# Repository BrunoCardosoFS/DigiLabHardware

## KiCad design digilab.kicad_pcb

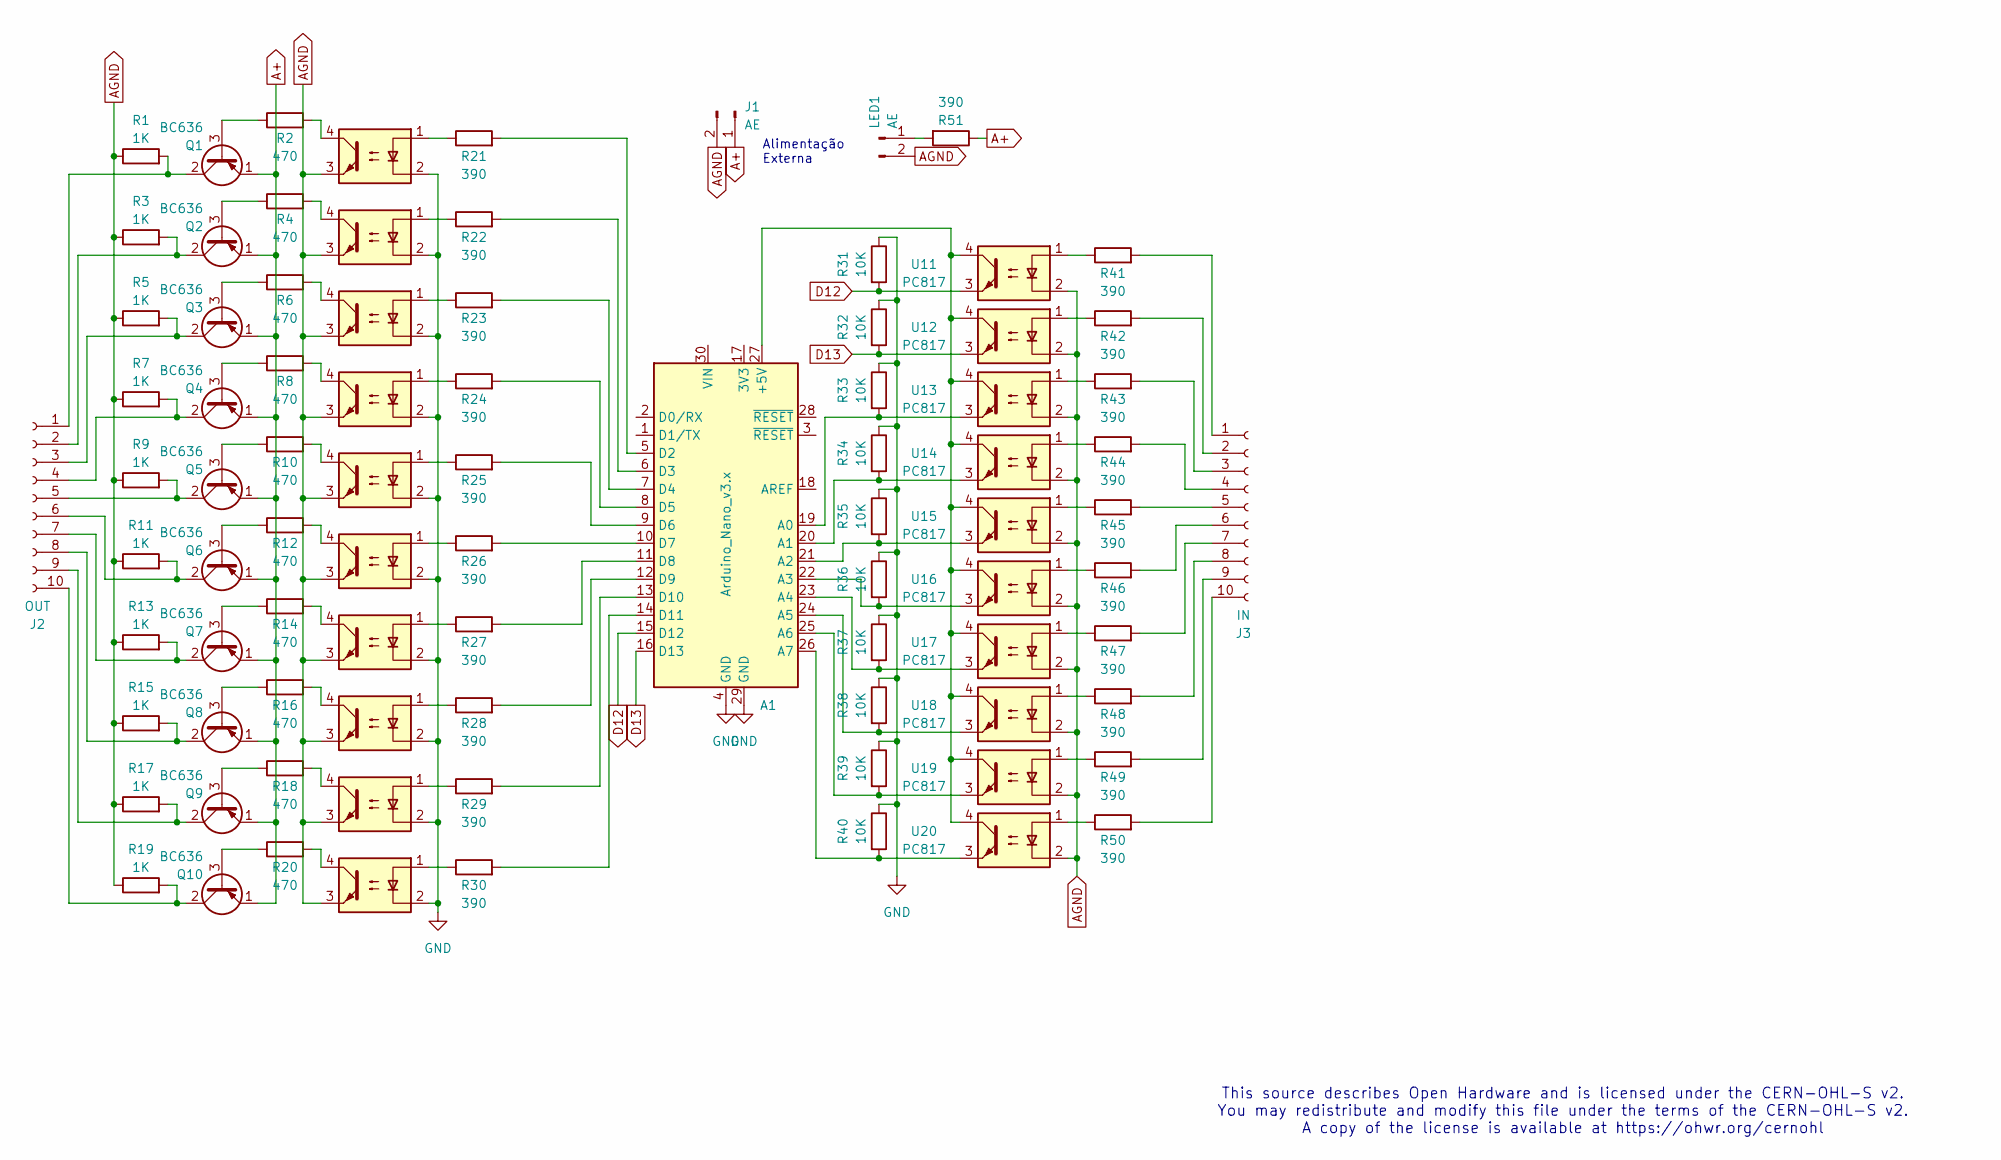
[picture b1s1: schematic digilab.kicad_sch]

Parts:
A1: Arduino_Nano_v3.x; Arduino_Nano
J1: AE; PinHeader_1x02_P2.54mm_Vertical
J2: OUT; PinSocket_1x10_P2.54mm_Vertical
J3: IN; PinSocket_1x10_P2.54mm_Vertical
LED1: AE; PinHeader_1x02_P2.54mm_Vertical
Q1, Q2, Q3, Q4, Q5, Q6, Q7, Q8, Q9, Q10: BC636; TO-92_Wide
R1, R3, R5, R7, R9, R11, R13, R15, R17, R19: 1K; R_Axial_DIN0204_L3.6mm_D1.6mm_P7.62mm_Horizontal
R2, R4, R6, R8, R10, R12, R14, R16, R18, R20: 470; R_Axial_DIN0204_L3.6mm_D1.6mm_P7.62mm_Horizontal
R21, R22, R23, R24, R25, R26, R27, R28, R29, R30, R41, R42, R43, R44, R45, R46, R47, R48, R49, R50, R51: 390; R_Axial_DIN0204_L3.6mm_D1.6mm_P7.62mm_Horizontal
R31, R32, R33, R34, R35, R36, R37, R38, R39, R40: 10K; R_Axial_DIN0204_L3.6mm_D1.6mm_P7.62mm_Horizontal
U1, U2, U3, U4, U5, U6, U7, U8, U9, U10, U11, U12, U13, U14, U15, U16, U17, U18, U19, U20: PC817; DIP-4_W7.62mm

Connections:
A+: J1.1, Q1.1 (E), Q2.1 (E), Q3.1 (E), Q4.1 (E), Q5.1 (E), Q6.1 (E), Q7.1 (E), Q8.1 (E), Q9.1 (E), Q10.1 (E), R51.1
AGND: J1.2, LED1.2, R1.1, R3.1, R5.1, R7.1, R9.1, R11.1, R13.1, R15.1, R17.1, R19.1, U1.3, U2.3, U3.3, U4.3, U5.3, U6.3, U7.3, U8.3, U9.3, U10.3, U11.2, U12.2, U13.2, U14.2, U15.2, U16.2, U17.2, U18.2, U19.2, U20.2
D12: A1.15 (D12), R31.2, U11.3
D13: A1.16 (D13), R32.2, U12.3
GND: A1.4 (GND), A1.29 (GND), R31.1, R32.1, R33.1, R34.1, R35.1, R36.1, R37.1, R38.1, R39.1, R40.1, U1.2, U2.2, U3.2, U4.2, U5.2, U6.2, U7.2, U8.2, U9.2, U10.2
unnamed: A1.27 (+5V), U11.4, U12.4, U13.4, U14.4, U15.4, U16.4, U17.4, U18.4, U19.4, U20.4
unnamed: A1.19 (A0), R33.2, U13.3
unnamed: A1.20 (A1), R34.2, U14.3
unnamed: A1.21 (A2), R35.2, U15.3
unnamed: A1.22 (A3), R36.2, U16.3
unnamed: A1.23 (A4), R37.2, U17.3
unnamed: A1.24 (A5), R38.2, U18.3
unnamed: A1.25 (A6), R39.2, U19.3
unnamed: A1.26 (A7), R40.2, U20.3
unnamed: A1.5 (D2), R21.2
unnamed: A1.6 (D3), R22.2
unnamed: A1.7 (D4), R23.2
unnamed: A1.8 (D5), R24.2
unnamed: A1.9 (D6), R25.2
unnamed: A1.10 (D7), R26.2
unnamed: A1.11 (D8), R27.2
unnamed: A1.12 (D9), R28.2
unnamed: A1.13 (D10), R29.2
unnamed: A1.14 (D11), R30.2
unnamed: J2.1, Q1.2 (C), R1.2
unnamed: J2.2, Q2.2 (C), R3.2
unnamed: J2.3, Q3.2 (C), R5.2
unnamed: J2.4, Q4.2 (C), R7.2
unnamed: J2.5, Q5.2 (C), R9.2
unnamed: J2.6, Q6.2 (C), R11.2
unnamed: J2.7, Q7.2 (C), R13.2
unnamed: J2.8, Q8.2 (C), R15.2
unnamed: J2.9, Q9.2 (C), R17.2
unnamed: J2.10, Q10.2 (C), R19.2
unnamed: J3.1, R41.2
unnamed: J3.2, R42.2
unnamed: J3.3, R43.2
unnamed: J3.4, R44.2
unnamed: J3.5, R45.2
unnamed: J3.6, R46.2
unnamed: J3.7, R47.2
unnamed: J3.8, R48.2
unnamed: J3.9, R49.2
unnamed: J3.10, R50.2
unnamed: LED1.1, R51.2
unnamed: Q1.3 (B), R2.1
unnamed: Q2.3 (B), R4.1
unnamed: Q3.3 (B), R6.1
unnamed: Q4.3 (B), R8.1
unnamed: Q5.3 (B), R10.1
unnamed: Q6.3 (B), R12.1
unnamed: Q7.3 (B), R14.1
unnamed: Q8.3 (B), R16.1
unnamed: Q9.3 (B), R18.1
unnamed: Q10.3 (B), R20.1
unnamed: R2.2, U1.4
unnamed: R4.2, U2.4
unnamed: R6.2, U3.4
unnamed: R8.2, U4.4
unnamed: R10.2, U5.4
unnamed: R12.2, U6.4
unnamed: R14.2, U7.4
unnamed: R16.2, U8.4
unnamed: R18.2, U9.4
unnamed: R20.2, U10.4
unnamed: R21.1, U1.1
unnamed: R22.1, U2.1
unnamed: R23.1, U3.1
unnamed: R24.1, U4.1
unnamed: R25.1, U5.1
unnamed: R26.1, U6.1
unnamed: R27.1, U7.1
unnamed: R28.1, U8.1
unnamed: R29.1, U9.1
unnamed: R30.1, U10.1
unnamed: R41.1, U11.1
unnamed: R42.1, U12.1
unnamed: R43.1, U13.1
unnamed: R44.1, U14.1
unnamed: R45.1, U15.1
unnamed: R46.1, U16.1
unnamed: R47.1, U17.1
unnamed: R48.1, U18.1
unnamed: R49.1, U19.1
unnamed: R50.1, U20.1

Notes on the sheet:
Alimentação Externa
This source describes Open Hardware and is licensed under the CERN-OHL-S v2. You may redistribute and modify this file under the terms of the CERN-OHL-S v2. A copy of the license is available at https://ohwr.org/cernohl

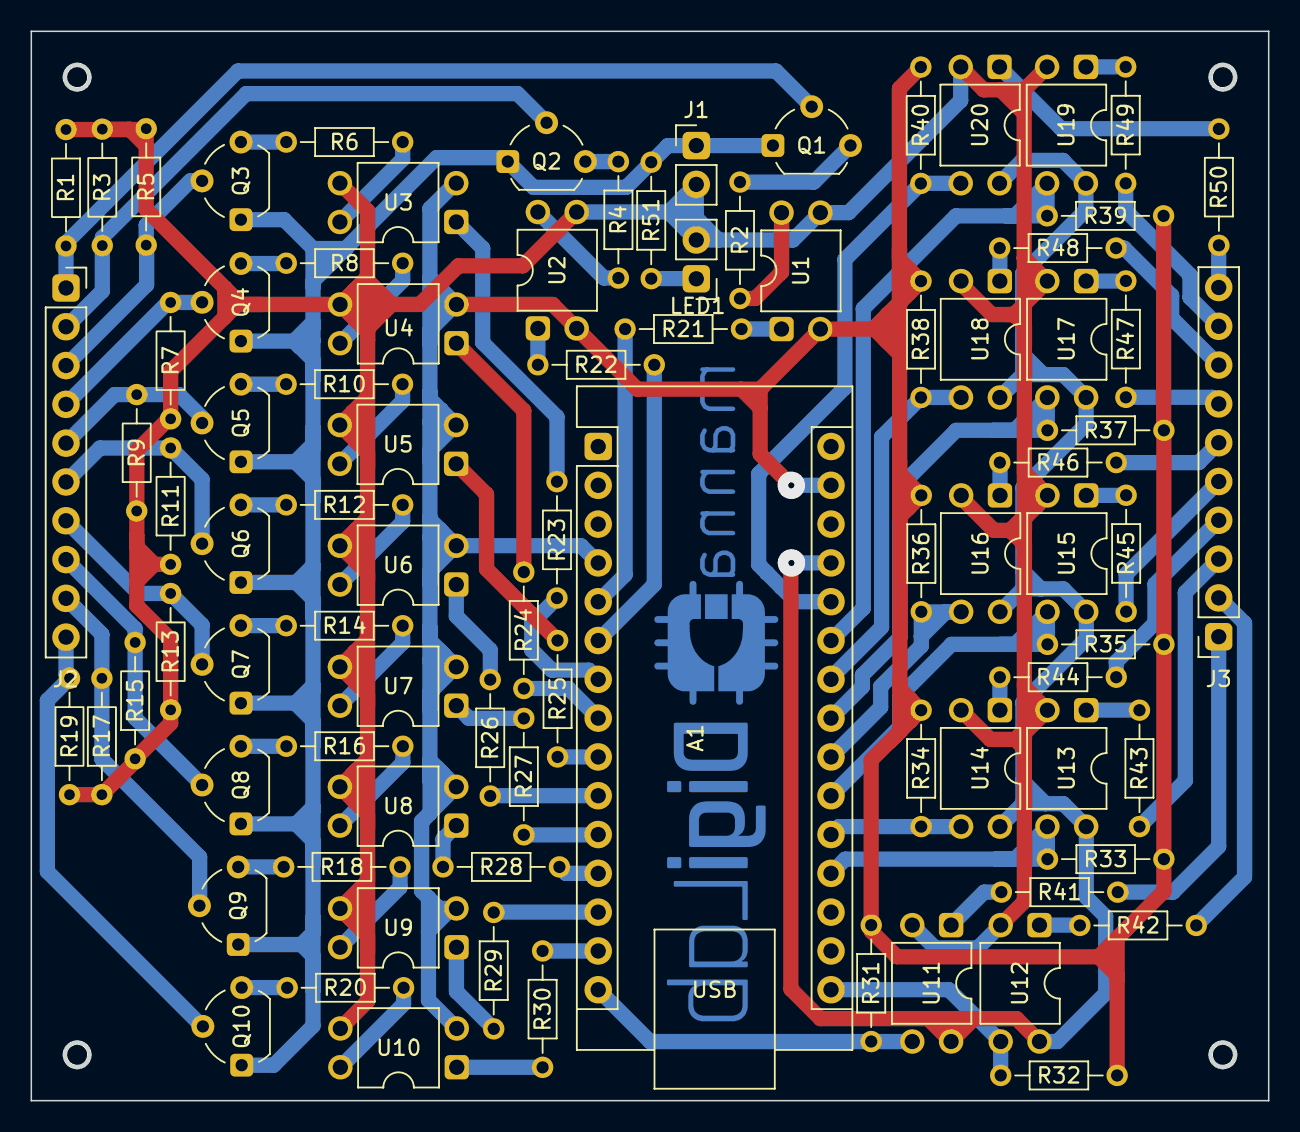
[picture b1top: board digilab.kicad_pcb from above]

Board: 2 copper layers, 80.8 x 69.8 mm, 86 parts (0 on the bottom side), 85 nets.

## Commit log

2025-06-28 DigiLab V1.0
